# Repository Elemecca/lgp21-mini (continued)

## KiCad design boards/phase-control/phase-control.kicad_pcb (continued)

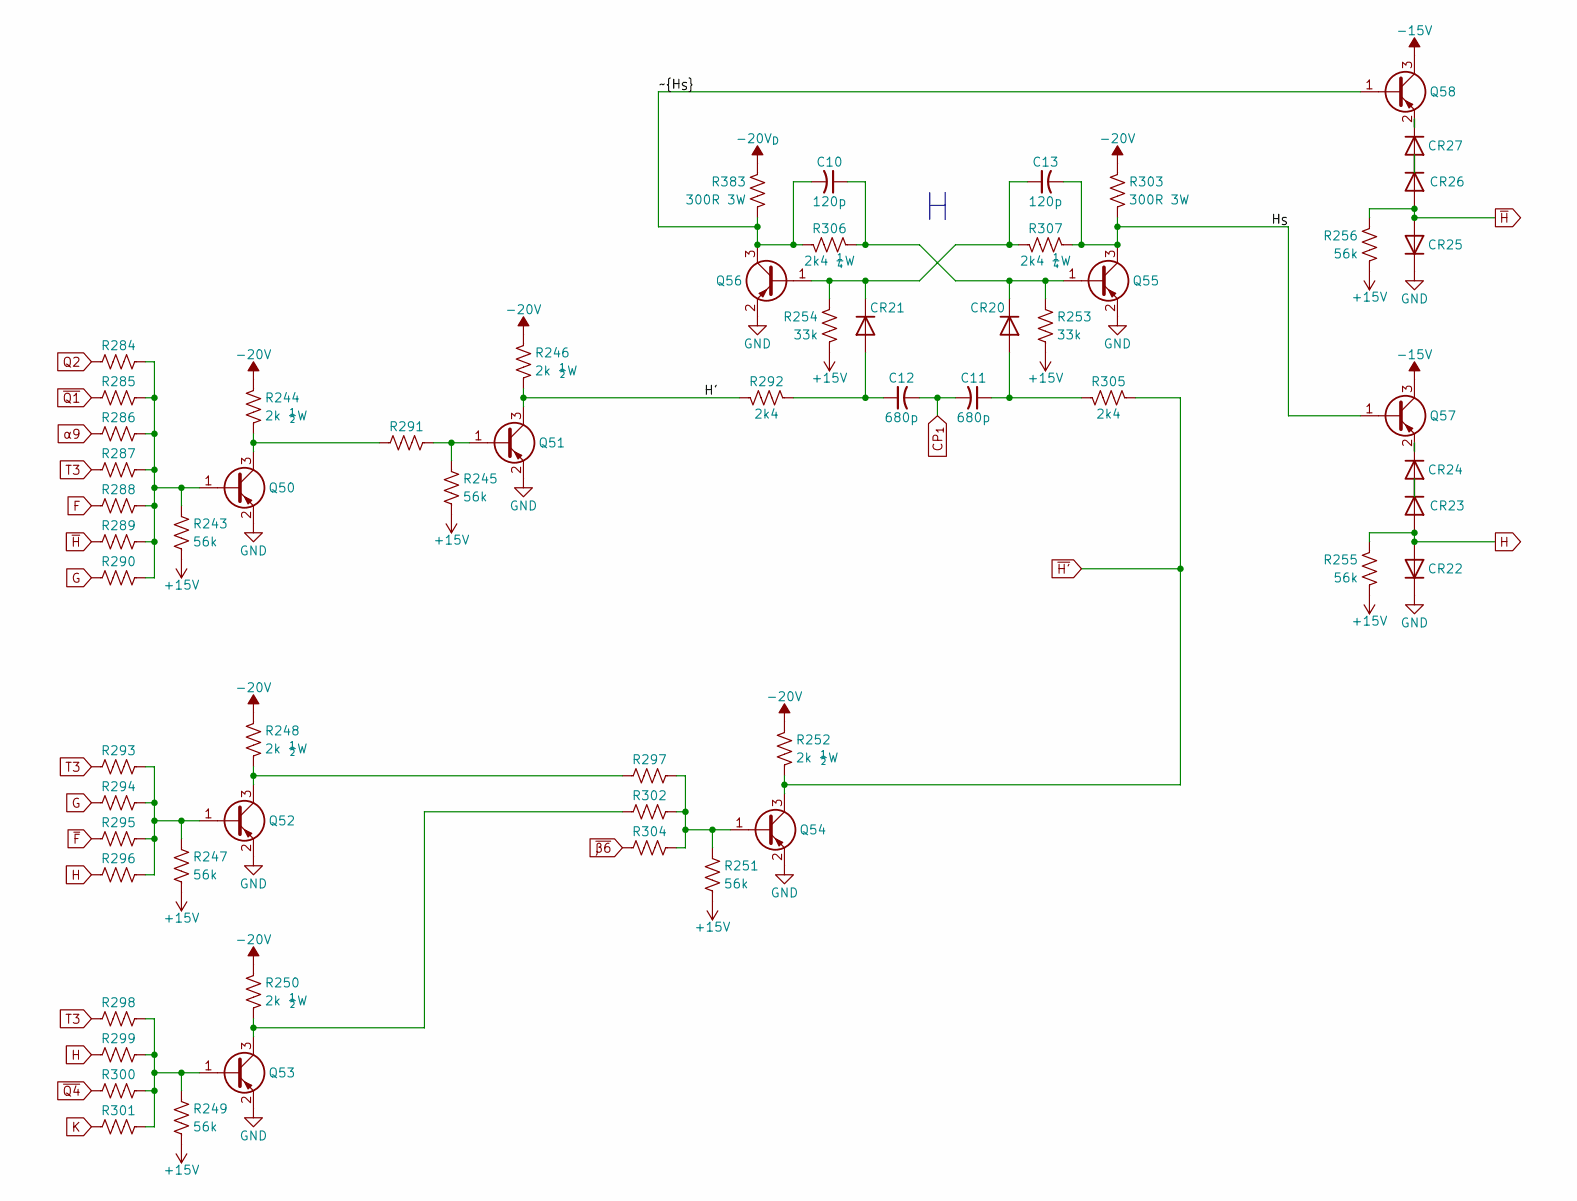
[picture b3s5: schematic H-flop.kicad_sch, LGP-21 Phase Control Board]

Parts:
C10, C13: 120p; C_0402_1005Metric
C11, C12: 680p; C_0402_1005Metric
CR20, CR21, CR22, CR23, CR24, CR25, CR26, CR27: 1N4148WS; D_SOD-323; LCSC C2128
Q50, Q51, Q52, Q53, Q54, Q55, Q56, Q57, Q58: MMBT5401; SOT-23; LCSC C8326
R243, R245, R247, R249, R251, R255, R256: 56k; R_0402_1005Metric
R244, R246, R248, R250, R252: 2k ½W; R_1210_3225Metric
R253, R254: 33k; R_0402_1005Metric
R284, R285, R286, R287, R288, R289, R290, R291, R293, R294, R295, R296, R297, R298, R299, R300, R301, R302, R304: 15k; R_0402_1005Metric
R292, R305: 2k4; R_0402_1005Metric
R303, R383: 300R 3W; R_Axial_DIN0516_L15.5mm_D5.0mm_P20.32mm_Horizontal
R306, R307: 2k4 ¼W; R_0603_1608Metric

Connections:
+15V: R243.2, R245.2, R247.2, R249.2, R251.2, R253.2, R254.2, R255.2, R256.2; also elsewhere on the board
-15V: Q57.3 (C), Q58.3 (C); also elsewhere on the board
-20V: R244.1, R246.1, R248.1, R250.1, R252.1, R303.1; also elsewhere on the board
-20V_{D}: R383.1; also elsewhere on the board
/H Flip-Flop/H': Q51.3 (C), R246.2, R292.1
/H Flip-Flop/H_{S}: C13.2, Q55.3 (C), Q57.1 (B), R303.2, R307.2
/H Flip-Flop/~H_{S}: C10.2, Q56.3 (C), Q58.1 (B), R306.1, R383.2
CP_{1}: C11.2, C12.2; also elsewhere on the board
F: R288.1; also elsewhere on the board
G: R290.1, R294.1; also elsewhere on the board
GND: CR22.1 (K), CR25.1 (K), Q50.2 (E), Q51.2 (E), Q52.2 (E), Q53.2 (E), Q54.2 (E), Q55.2 (E), Q56.2 (E); also elsewhere on the board
H: CR22.2 (A), CR23.2 (A), R255.1, R296.1, R299.1; also elsewhere on the board
K: R301.1; also elsewhere on the board
unnamed: C11.1, CR20.2 (A), R305.1
unnamed: C10.1, CR20.1 (K), Q55.1 (B), R253.1, R306.2
unnamed: C12.1, CR21.2 (A), R292.2
unnamed: C13.1, CR21.1 (K), Q56.1 (B), R254.1, R307.1
unnamed: CR23.1 (K), CR24.2 (A)
unnamed: CR24.1 (K), Q57.2 (E)
unnamed: CR26.1 (K), CR27.2 (A)
unnamed: CR27.1 (K), Q58.2 (E)
unnamed: Q50.1 (B), R243.1, R284.2, R285.2, R286.2, R287.2, R288.2, R289.2, R290.2
unnamed: Q50.3 (C), R244.2, R291.1
unnamed: Q51.1 (B), R245.1, R291.2
unnamed: Q52.1 (B), R247.1, R293.2, R294.2, R295.2, R296.2
unnamed: Q52.3 (C), R248.2, R297.1
unnamed: Q53.1 (B), R249.1, R298.2, R299.2, R300.2, R301.2
unnamed: Q53.3 (C), R250.2, R302.1
unnamed: Q54.1 (B), R251.1, R297.2, R302.2, R304.2
Q2: R284.1; also elsewhere on the board
T3: R287.1, R293.1, R298.1; also elsewhere on the board
~F: R295.1; also elsewhere on the board
~H': Q54.3 (C), R252.2, R305.2; also elsewhere on the board
~H: CR25.2 (A), CR26.2 (A), R256.1, R289.1; also elsewhere on the board
~Q1: R285.1; also elsewhere on the board
~Q4: R300.1; also elsewhere on the board
~β6: R304.1; also elsewhere on the board
α9: R286.1; also elsewhere on the board

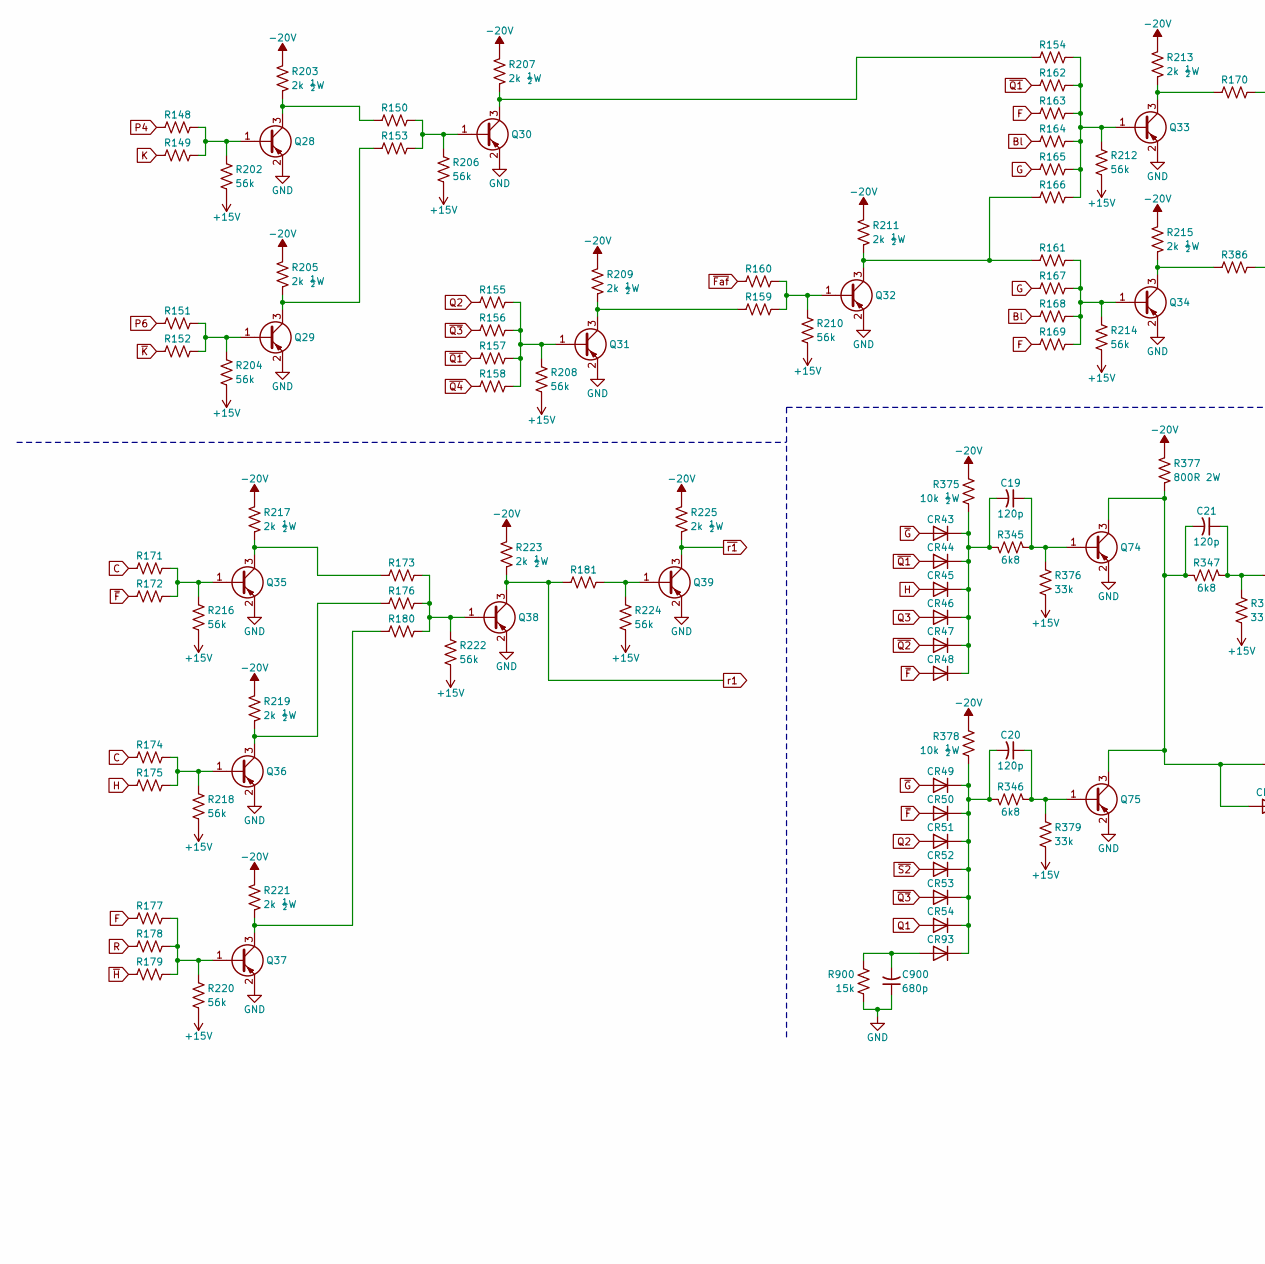
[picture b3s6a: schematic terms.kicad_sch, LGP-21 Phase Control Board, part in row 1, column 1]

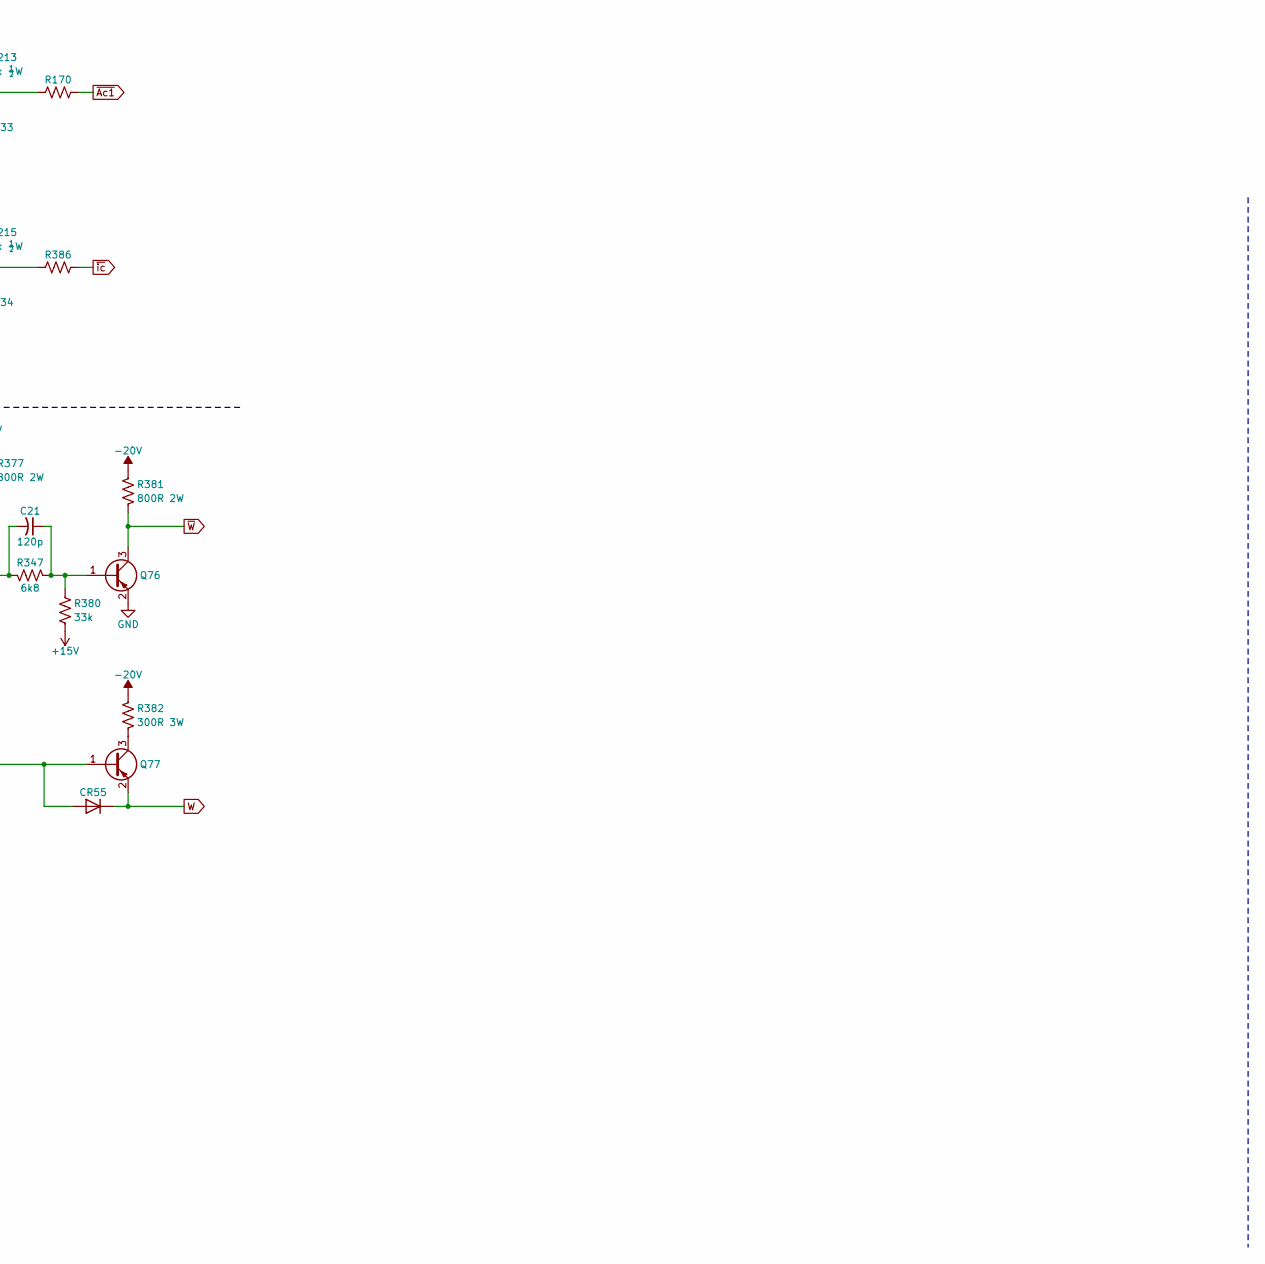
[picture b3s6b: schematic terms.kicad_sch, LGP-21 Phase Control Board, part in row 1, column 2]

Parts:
C19, C20, C21: 120p; C_0402_1005Metric
C900: 680p; C_0402_1005Metric
CR43, CR44, CR45, CR46, CR47, CR48, CR49, CR50, CR51, CR52, CR53, CR54, CR55, CR93: 1N4148WS; D_SOD-323; LCSC C2128
Q28, Q29, Q30, Q31, Q32, Q33, Q34, Q35, Q36, Q37, Q38, Q39, Q74, Q75, Q76, Q77: MMBT5401; SOT-23; LCSC C8326
R148, R149, R150, R151, R152, R153, R154, R155, R156, R157, R158, R159, R160, R161, R162, R163, R164, R165, R166, R167, R168, R169, R170, R171, R172, R173, R174, R175, R176, R177, R178, R179, R180, R181, R386, R900: 15k; R_0402_1005Metric
R202, R204, R206, R208, R210, R212, R214, R216, R218, R220, R222, R224: 56k; R_0402_1005Metric
R203, R205, R207, R209, R211, R213, R215, R217, R219, R221, R223, R225: 2k ½W; R_1210_3225Metric
R345, R346, R347: 6k8; R_0402_1005Metric
R375, R378: 10k ½W; R_1210_3225Metric
R376, R379, R380: 33k; R_0402_1005Metric
R377, R381: 800R 2W; R_Axial_DIN0516_L15.5mm_D5.0mm_P20.32mm_Horizontal
R382: 300R 3W; R_Axial_DIN0516_L15.5mm_D5.0mm_P20.32mm_Horizontal

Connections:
+15V: R202.2, R204.2, R206.2, R208.2, R210.2, R212.2, R214.2, R216.2, R218.2, R220.2, R222.2, R224.2, R376.2, R379.2, R380.2; also elsewhere on the board
-20V: R203.1, R205.1, R207.1, R209.1, R211.1, R213.1, R215.1, R217.1, R219.1, R221.1, R223.1, R225.1, R375.1, R377.1, R378.1, R381.1, R382.1; also elsewhere on the board
Bl: R164.1, R168.1; also elsewhere on the board
C: R171.1, R174.1; also elsewhere on the board
F: R163.1, R169.1, R177.1; also elsewhere on the board
G: R165.1, R167.1; also elsewhere on the board
GND: C900.1, Q28.2 (E), Q29.2 (E), Q30.2 (E), Q31.2 (E), Q32.2 (E), Q33.2 (E), Q34.2 (E), Q35.2 (E), Q36.2 (E), Q37.2 (E), Q38.2 (E), Q39.2 (E), Q74.2 (E), Q75.2 (E), Q76.2 (E), R900.2; also elsewhere on the board
H: CR45.2 (A), R175.1; also elsewhere on the board
K: R149.1; also elsewhere on the board
unnamed: C19.2, CR43.1 (K), CR44.1 (K), CR45.1 (K), CR46.1 (K), CR47.1 (K), CR48.1 (K), R345.1, R375.2
unnamed: C20.2, CR49.1 (K), CR50.1 (K), CR51.1 (K), CR52.1 (K), CR53.1 (K), CR54.1 (K), CR93.1 (K), R346.1, R378.2
unnamed: C21.2, CR55.2 (A), Q74.3 (C), Q75.3 (C), Q77.1 (B), R347.1, R377.2
unnamed: C900.2, CR93.2 (A), R900.1
unnamed: Q28.1 (B), R148.2, R149.2, R202.1
unnamed: Q28.3 (C), R150.1, R203.2
unnamed: Q29.1 (B), R151.2, R152.2, R204.1
unnamed: Q29.3 (C), R153.1, R205.2
unnamed: Q30.1 (B), R150.2, R153.2, R206.1
unnamed: Q30.3 (C), R154.1, R207.2
unnamed: Q31.1 (B), R155.2, R156.2, R157.2, R158.2, R208.1
unnamed: Q31.3 (C), R159.1, R209.2
unnamed: Q32.1 (B), R159.2, R160.2, R210.1
unnamed: Q32.3 (C), R161.1, R166.1, R211.2
unnamed: Q33.1 (B), R154.2, R162.2, R163.2, R164.2, R165.2, R166.2, R212.1
unnamed: Q33.3 (C), R170.1, R213.2
unnamed: Q34.1 (B), R161.2, R167.2, R168.2, R169.2, R214.1
unnamed: Q34.3 (C), R215.2, R386.1
unnamed: Q35.1 (B), R171.2, R172.2, R216.1
unnamed: Q35.3 (C), R173.1, R217.2
unnamed: Q36.1 (B), R174.2, R175.2, R218.1
unnamed: Q36.3 (C), R176.1, R219.2
unnamed: Q37.1 (B), R177.2, R178.2, R179.2, R220.1
unnamed: Q37.3 (C), R180.1, R221.2
unnamed: Q38.1 (B), R173.2, R176.2, R180.2, R222.1
unnamed: Q39.1 (B), R181.2, R224.1
unnamed: C19.1, Q74.1 (B), R345.2, R376.1
unnamed: C20.1, Q75.1 (B), R346.2, R379.1
unnamed: C21.1, Q76.1 (B), R347.2, R380.1
unnamed: Q77.3 (C), R382.2
P4: R148.1; also elsewhere on the board
P6: R151.1; also elsewhere on the board
Q1: CR54.2 (A); also elsewhere on the board
Q2: CR51.2 (A), R155.1; also elsewhere on the board
Q3: CR46.2 (A); also elsewhere on the board
R: R178.1; also elsewhere on the board
W: CR55.1 (K), Q77.2 (E); also elsewhere on the board
r1: Q38.3 (C), R181.1, R223.2; also elsewhere on the board
~Ac1: R170.2; also elsewhere on the board
~Faf: R160.1; also elsewhere on the board
~F: CR48.2 (A), CR50.2 (A), R172.1; also elsewhere on the board
~G: CR43.2 (A), CR49.2 (A); also elsewhere on the board
~H: R179.1; also elsewhere on the board
~K: R152.1; also elsewhere on the board
~Q1: CR44.2 (A), R157.1, R162.1; also elsewhere on the board
~Q2: CR47.2 (A); also elsewhere on the board
~Q3: CR53.2 (A), R156.1; also elsewhere on the board
~Q4: R158.1; also elsewhere on the board
~S2: CR52.2 (A); also elsewhere on the board
~W: Q76.3 (C), R381.2; also elsewhere on the board
~ic: R386.2; also elsewhere on the board
~r1: Q39.3 (C), R225.2; also elsewhere on the board

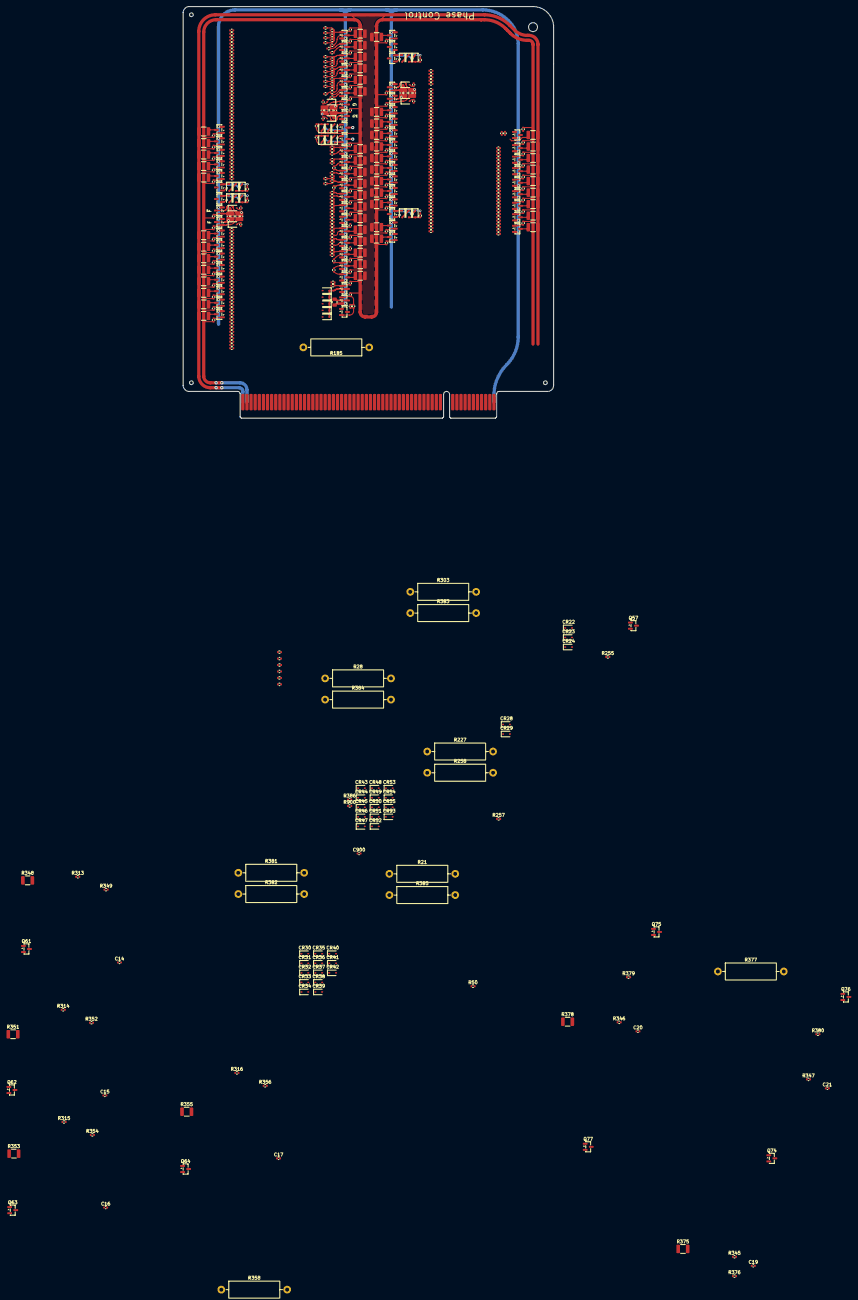
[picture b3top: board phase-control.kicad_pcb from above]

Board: 2 copper layers, 114.3 x 127.0 mm, 558 parts (1 on the bottom side), 228 nets.

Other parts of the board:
MH1: Bivar CP-26 WE; Bivar_CP-26_WE
TH1, TH2, TH2#2: Tooling Hole; JLC_ToolingHole

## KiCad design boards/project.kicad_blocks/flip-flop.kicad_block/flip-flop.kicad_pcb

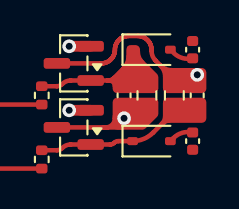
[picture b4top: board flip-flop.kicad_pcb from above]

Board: 2 copper layers, 12 parts (0 on the bottom side), 9 nets.

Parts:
C1, C4: 120p; C_0402_1005Metric
C2, C3: 680p; C_0402_1005Metric
CR1, CR2: 1N4148WS; D_SOD-323
Q1, Q2: MMBT5401; SOT-23
R1, R3: 2k4 ¼W; R_0603_1608Metric
R2, R4: 33k; R_0402_1005Metric

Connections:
+15V: R2.2, R4.2
GND: Q1.2 (E), Q2.2 (E)
unnamed: C2.2, C3.2
unnamed: C2.1, CR1.2 (A)
unnamed: C4.1, CR1.1 (K), Q1.1 (B), R2.1, R3.1
unnamed: C3.1, CR2.2 (A)
unnamed: C1.1, CR2.1 (K), Q2.1 (B), R1.2, R4.1
unnamed: C1.2, Q1.3 (C), R1.1
unnamed: C4.2, Q2.3 (C), R3.2

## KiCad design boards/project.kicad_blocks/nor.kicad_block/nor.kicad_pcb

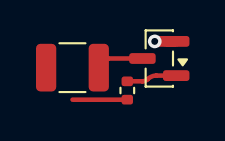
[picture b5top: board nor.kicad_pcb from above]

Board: 2 copper layers, 3 parts (0 on the bottom side), 2 nets.

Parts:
Q20: MMBT5401; SOT-23
R35: 56k; R_0402_1005Metric
R36: 2k ½W; R_1210_3225Metric

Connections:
unnamed: Q20.1 (B), R35.1
unnamed: Q20.3 (C), R36.2

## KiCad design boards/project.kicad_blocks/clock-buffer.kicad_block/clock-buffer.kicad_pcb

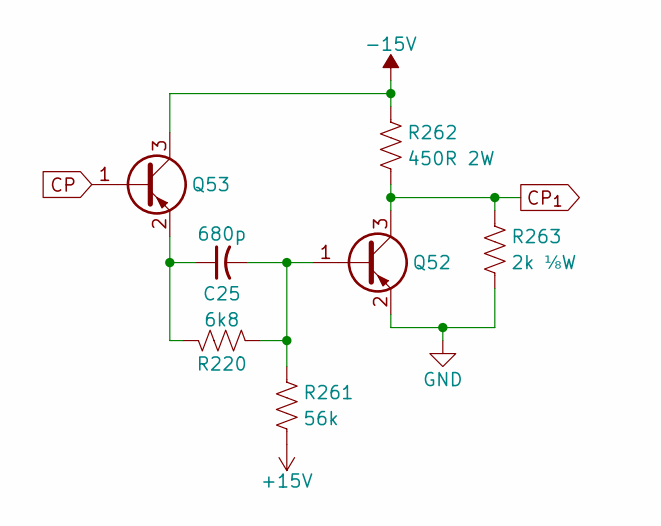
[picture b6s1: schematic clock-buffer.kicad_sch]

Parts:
C25: 680p; C_0402_1005Metric
Q52, Q53: MMBT5401; SOT-23
R220: 6k8; R_0402_1005Metric
R261: 56k; R_0402_1005Metric
R262: 450R 2W; R_Axial_DIN0516_L15.5mm_D5.0mm_P20.32mm_Horizontal
R263: 2k ⅛W; R_0805_2012Metric

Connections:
+15V: R261.2
-15V: Q53.3 (C), R262.1
CP: Q53.1 (B)
CP_{1}: Q52.3 (C), R262.2, R263.1
GND: Q52.2 (E), R263.2
unnamed: C25.2, Q52.1 (B), R220.2, R261.1
unnamed: C25.1, Q53.2 (E), R220.1

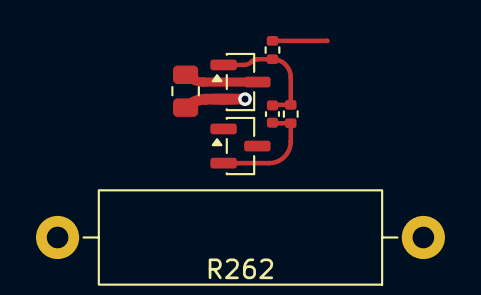
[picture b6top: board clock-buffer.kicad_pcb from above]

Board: 2 copper layers, 7 parts (0 on the bottom side), 5 nets.

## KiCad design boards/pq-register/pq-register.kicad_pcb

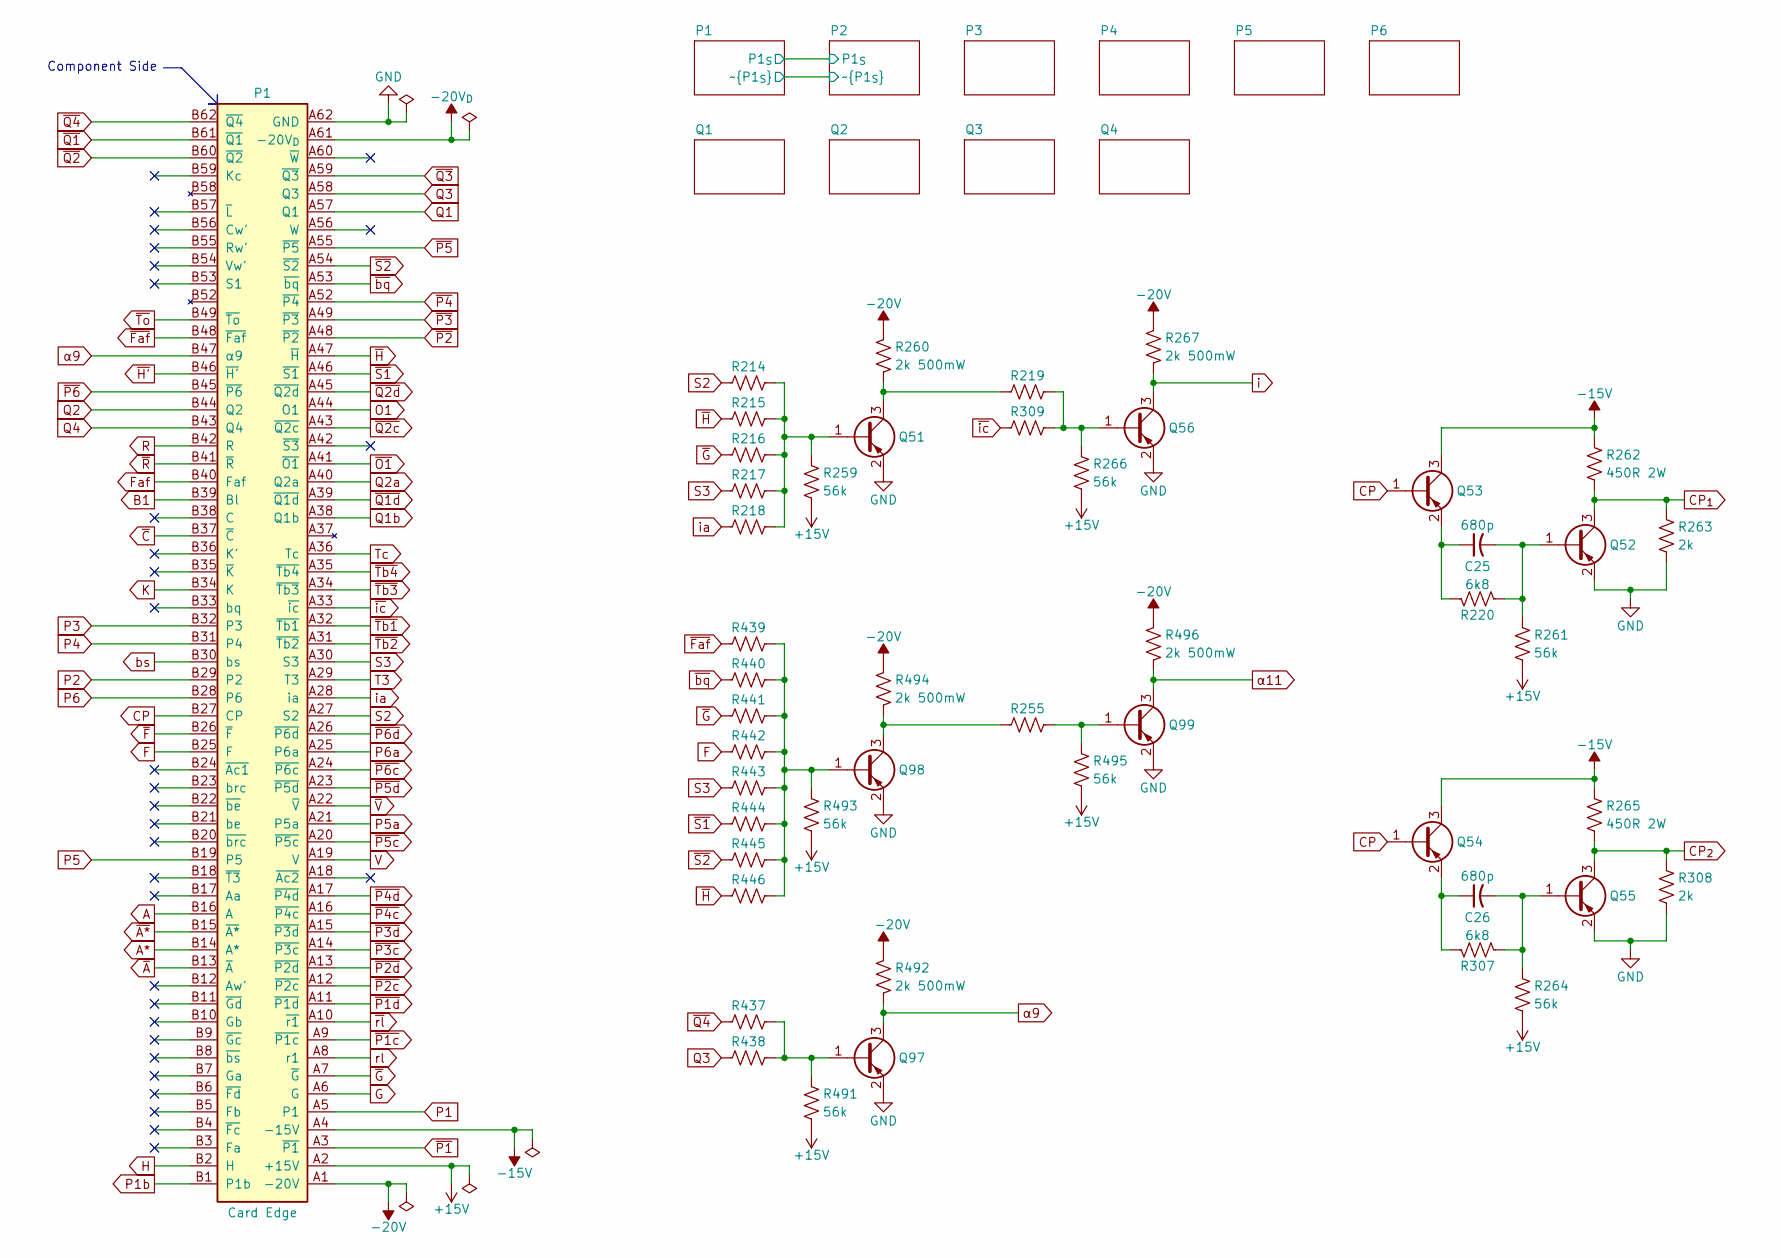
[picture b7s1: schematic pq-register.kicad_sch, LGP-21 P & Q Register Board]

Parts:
C25, C26: 680p; C_0402_1005Metric
P1: Card Edge; Bus_PCI_5V_32bit
Q51, Q52, Q53, Q54, Q55, Q56, Q97, Q98, Q99: MMBT5401; SOT-23
R214, R215, R216, R217, R218, R219, R255, R309, R437, R438, R439, R440, R441, R442, R443, R444, R445, R446: 15k; R_0402_1005Metric
R220, R307: 6k8; R_0402_1005Metric
R259, R261, R264, R266, R491, R493, R495: 56k; R_0402_1005Metric
R260, R267, R492, R494, R496: 2k 500mW; R_1210_3225Metric
R262, R265: 450R 2W; R_Axial_DIN0516_L15.5mm_D5.0mm_P20.32mm_Horizontal
R263, R308: 2k; R_1206_3216Metric

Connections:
+15V: P1.A2 (+15V), R259.2, R261.2, R264.2, R266.2, R491.2, R493.2, R495.2; also elsewhere on the board
-15V: P1.A4 (-15V), Q53.3 (C), Q54.3 (C), R262.1, R265.1; also elsewhere on the board
-20V: P1.A1 (-20V), R260.1, R267.1, R492.1, R494.1, R496.1; also elsewhere on the board
-20V_{D}: P1.A61 (-20V_{D}); also elsewhere on the board
A: P1.B16 (A); also elsewhere on the board
A*: P1.B14 (A*); also elsewhere on the board
B1: P1.B39 (Bl); also elsewhere on the board
CP: P1.B27 (CP), Q53.1 (B), Q54.1 (B)
CP_{1}: Q52.3 (C), R262.2, R263.1; also elsewhere on the board
CP_{2}: Q55.3 (C), R265.2, R308.1; also elsewhere on the board
F: P1.B25 (F), R442.1; also elsewhere on the board
Faf: P1.B40 (Faf); also elsewhere on the board
G: P1.A6 (G); also elsewhere on the board
GND: P1.A62 (GND), Q51.2 (E), Q52.2 (E), Q55.2 (E), Q56.2 (E), Q97.2 (E), Q98.2 (E), Q99.2 (E), R263.2, R308.2; also elsewhere on the board
H: P1.B2 (H); also elsewhere on the board
K: P1.B34 (K); also elsewhere on the board
unnamed: Q51.1 (B), R214.2, R215.2, R216.2, R217.2, R218.2, R259.1
unnamed: Q51.3 (C), R219.1, R260.2
unnamed: C25.2, Q52.1 (B), R220.2, R261.1
unnamed: C25.1, Q53.2 (E), R220.1
unnamed: C26.1, Q54.2 (E), R307.1
unnamed: C26.2, Q55.1 (B), R264.1, R307.2
unnamed: Q56.1 (B), R219.2, R266.1, R309.2
unnamed: Q97.1 (B), R437.2, R438.2, R491.1
unnamed: Q98.1 (B), R439.2, R440.2, R441.2, R442.2, R443.2, R444.2, R445.2, R446.2, R493.1
unnamed: Q98.3 (C), R255.1, R494.2
unnamed: Q99.1 (B), R255.2, R495.1
O1: P1.A44 (O1); also elsewhere on the board
P1: P1.A5 (P1); also elsewhere on the board
P1b: P1.B1 (P1b); also elsewhere on the board
P2: P1.B29 (P2); also elsewhere on the board
P3: P1.B32 (P3); also elsewhere on the board
P4: P1.B31 (P4); also elsewhere on the board
P5: P1.B19 (P5); also elsewhere on the board
P5a: P1.A21 (P5a); also elsewhere on the board
P6: P1.B28 (P6); also elsewhere on the board
P6a: P1.A25 (P6a); also elsewhere on the board
Q1: P1.A57 (Q1); also elsewhere on the board
Q1b: P1.A38 (Q1b); also elsewhere on the board
Q2: P1.B44 (Q2); also elsewhere on the board
Q2a: P1.A40 (Q2a)
Q3: P1.A58 (Q3), R438.1; also elsewhere on the board
Q4: P1.B43 (Q4); also elsewhere on the board
R: P1.B42 (R); also elsewhere on the board
S2: P1.A27 (S2), R214.1
S3: P1.A30 (S3), R217.1, R443.1
T3: P1.A29 (T3); also elsewhere on the board
Tc: P1.A36 (Tc); also elsewhere on the board
V: P1.A19 (V); also elsewhere on the board
bs: P1.B30 (bs); also elsewhere on the board
i: Q56.3 (C), R267.2; also elsewhere on the board
ia: P1.A28 (ia), R218.1
rl: P1.A8 (r1); also elsewhere on the board
~A*: P1.B15 (~A*); also elsewhere on the board
~A: P1.B13 (~A); also elsewhere on the board
~C: P1.B37 (~C); also elsewhere on the board
~Faf: P1.B48 (~Faf), R439.1; also elsewhere on the board
~F: P1.B26 (~F); also elsewhere on the board
~G: P1.A7 (~G), R216.1, R441.1; also elsewhere on the board
~H': P1.B46 (~H'); also elsewhere on the board
~H: P1.A47 (~H), R215.1, R446.1; also elsewhere on the board
~O1: P1.A41 (~O1); also elsewhere on the board
~P1c: P1.A9 (~P1c); also elsewhere on the board
~P1d: P1.A11 (~P1d); also elsewhere on the board
~P1: P1.A3 (~P1); also elsewhere on the board
~P2c: P1.A12 (~P2c); also elsewhere on the board
~P2d: P1.A13 (~P2d); also elsewhere on the board
~P2: P1.A48 (~P2); also elsewhere on the board
~P3c: P1.A14 (~P3c); also elsewhere on the board
~P3d: P1.A15 (~P3d); also elsewhere on the board
~P3: P1.A49 (~P3); also elsewhere on the board
~P4c: P1.A16 (~P4c); also elsewhere on the board
~P4d: P1.A17 (~P4d); also elsewhere on the board
~P4: P1.A52 (~P4); also elsewhere on the board
~P5c: P1.A20 (~P5c); also elsewhere on the board
~P5d: P1.A23 (~P5d); also elsewhere on the board
~P5: P1.A55 (~P5); also elsewhere on the board
~P6c: P1.A24 (~P6c); also elsewhere on the board
~P6d: P1.A26 (~P6d); also elsewhere on the board
~P6: P1.B45 (~P6); also elsewhere on the board
~Q1d: P1.A39 (~Q1d); also elsewhere on the board
~Q1: P1.B61 (~Q1); also elsewhere on the board
~Q2c: P1.A43 (~Q2c); also elsewhere on the board
~Q2d: P1.A45 (~Q2d); also elsewhere on the board
~Q2: P1.B60 (~Q2); also elsewhere on the board
~Q3: P1.A59 (~Q3); also elsewhere on the board
~Q4: P1.B62 (~Q4), R437.1; also elsewhere on the board
~R: P1.B41 (~R); also elsewhere on the board
~S1: P1.A46 (~S1), R444.1
~S2: P1.A54 (~S2), R445.1
~Tb1: P1.A32 (~Tb1); also elsewhere on the board
~Tb2: P1.A31 (~Tb2); also elsewhere on the board
~Tb3: P1.A34 (~Tb3); also elsewhere on the board
~Tb4: P1.A35 (~Tb4); also elsewhere on the board
~To: P1.B49 (~To); also elsewhere on the board
~V: P1.A22 (~V); also elsewhere on the board
~bq: P1.A53 (~bq), R440.1; also elsewhere on the board
~ic: P1.A33 (~ic), R309.1
~rl: P1.A10 (~r1); also elsewhere on the board
α9: P1.B47 (α9), Q97.3 (C), R492.2
α11: Q99.3 (C), R496.2; also elsewhere on the board

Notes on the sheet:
Component Side

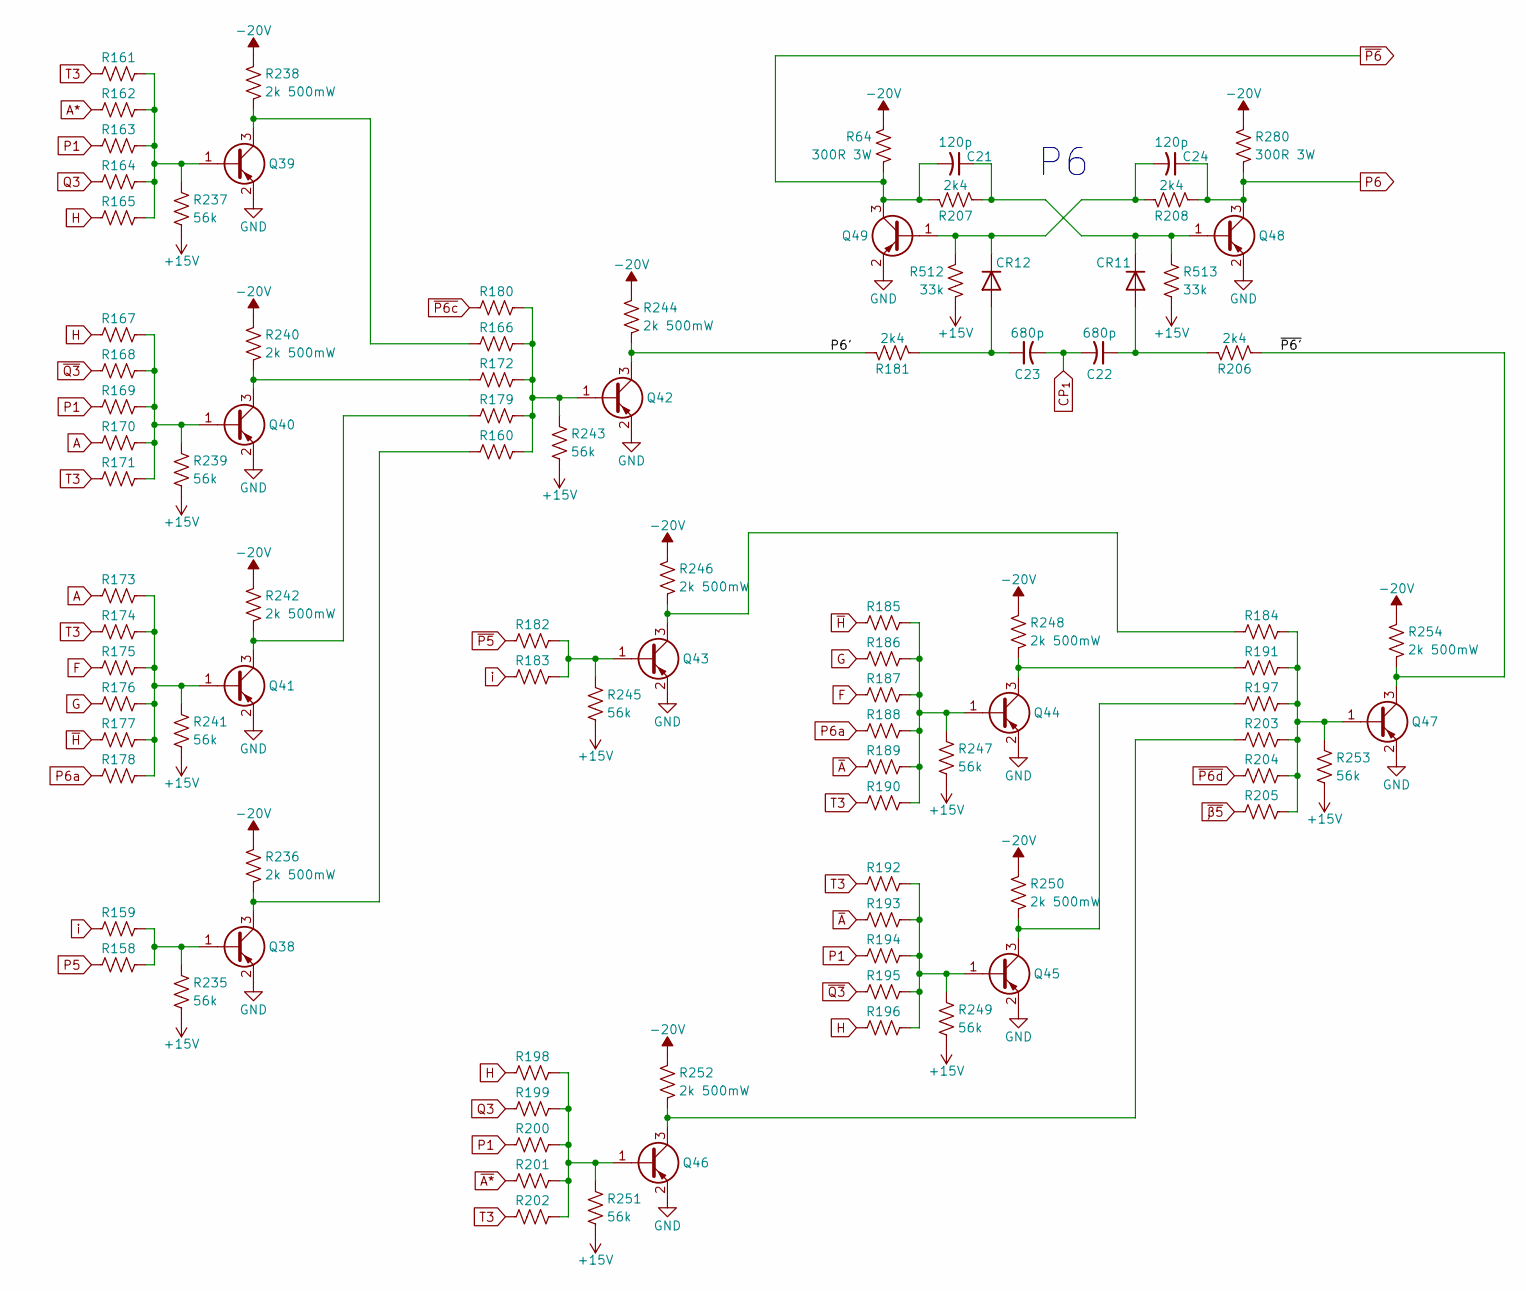
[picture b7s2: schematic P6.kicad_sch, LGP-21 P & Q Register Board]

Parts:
C21, C24: 120p; C_0402_1005Metric
C22, C23: 680p; C_0402_1005Metric
CR11, CR12: 1N5819WS; D_SOD-323
Q38, Q39, Q40, Q41, Q42, Q43, Q44, Q45, Q46, Q47, Q48, Q49: MMBT5401; SOT-23
R64, R280: 300R 3W; R_Axial_DIN0516_L15.5mm_D5.0mm_P20.32mm_Horizontal
R158, R159, R160, R161, R162, R163, R164, R165, R166, R167, R168, R169, R170, R171, R172, R173, R174, R175, R176, R177, R178, R179, R180, R182, R183, R184, R185, R186, R187, R188, R189, R190, R191, R192, R193, R194, R195, R196, R197, R198, R199, R200, R201, R202, R203, R204, R205: 15k; R_0402_1005Metric
R181, R206, R207, R208: 2k4; R_0402_1005Metric
R235, R237, R239, R241, R243, R245, R247, R249, R251, R253: 56k; R_0402_1005Metric
R236, R238, R240, R242, R244, R246, R248, R250, R252, R254: 2k 500mW; R_1210_3225Metric
R512, R513: 33k; R_0402_1005Metric

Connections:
+15V: R235.2, R237.2, R239.2, R241.2, R243.2, R245.2, R247.2, R249.2, R251.2, R253.2, R512.2, R513.2; also elsewhere on the board
-20V: R64.1, R236.1, R238.1, R240.1, R242.1, R244.1, R246.1, R248.1, R250.1, R252.1, R254.1, R280.1; also elsewhere on the board
/P6/P6': Q42.3 (C), R181.1, R244.2
/P6/~P6': Q47.3 (C), R206.2, R254.2
A: R170.1, R173.1; also elsewhere on the board
A*: R162.1; also elsewhere on the board
CP_{1}: C22.2, C23.2; also elsewhere on the board
F: R175.1, R187.1; also elsewhere on the board
G: R176.1, R186.1; also elsewhere on the board
GND: Q38.2 (E), Q39.2 (E), Q40.2 (E), Q41.2 (E), Q42.2 (E), Q43.2 (E), Q44.2 (E), Q45.2 (E), Q46.2 (E), Q47.2 (E), Q48.2 (E), Q49.2 (E); also elsewhere on the board
H: R165.1, R167.1, R196.1, R198.1; also elsewhere on the board
unnamed: C22.1, CR11.2 (A), R206.1
unnamed: C21.1, CR11.1 (K), Q48.1 (B), R207.2, R513.1
unnamed: C23.1, CR12.2 (A), R181.2
unnamed: C24.2, CR12.1 (K), Q49.1 (B), R208.1, R512.1
unnamed: Q38.1 (B), R158.2, R159.2, R235.1
unnamed: Q38.3 (C), R160.1, R236.2
unnamed: Q39.1 (B), R161.2, R162.2, R163.2, R164.2, R165.2, R237.1
unnamed: Q39.3 (C), R166.1, R238.2
unnamed: Q40.1 (B), R167.2, R168.2, R169.2, R170.2, R171.2, R239.1
unnamed: Q40.3 (C), R172.1, R240.2
unnamed: Q41.1 (B), R173.2, R174.2, R175.2, R176.2, R177.2, R178.2, R241.1
unnamed: Q41.3 (C), R179.1, R242.2
unnamed: Q42.1 (B), R160.2, R166.2, R172.2, R179.2, R180.2, R243.1
unnamed: Q43.1 (B), R182.2, R183.2, R245.1
unnamed: Q43.3 (C), R184.1, R246.2
unnamed: Q44.1 (B), R185.2, R186.2, R187.2, R188.2, R189.2, R190.2, R247.1
unnamed: Q44.3 (C), R191.1, R248.2
unnamed: Q45.1 (B), R192.2, R193.2, R194.2, R195.2, R196.2, R249.1
unnamed: Q45.3 (C), R197.1, R250.2
unnamed: Q46.1 (B), R198.2, R199.2, R200.2, R201.2, R202.2, R251.1
unnamed: Q46.3 (C), R203.1, R252.2
unnamed: Q47.1 (B), R184.2, R191.2, R197.2, R203.2, R204.2, R205.2, R253.1
P1: R163.1, R169.1, R194.1, R200.1; also elsewhere on the board
P5: R158.1; also elsewhere on the board
P6: C24.1, Q48.3 (C), R208.2, R280.2; also elsewhere on the board
P6a: R178.1, R188.1; also elsewhere on the board
Q3: R164.1, R199.1; also elsewhere on the board
T3: R161.1, R171.1, R174.1, R190.1, R192.1, R202.1; also elsewhere on the board
i: R159.1, R183.1; also elsewhere on the board
~A*: R201.1; also elsewhere on the board
~A: R189.1, R193.1; also elsewhere on the board
~H: R177.1, R185.1; also elsewhere on the board
~P5: R182.1; also elsewhere on the board
~P6c: R180.1; also elsewhere on the board
~P6d: R204.1; also elsewhere on the board
~P6: C21.2, Q49.3 (C), R64.2, R207.1; also elsewhere on the board
~Q3: R168.1, R195.1; also elsewhere on the board
~β5: R205.1
